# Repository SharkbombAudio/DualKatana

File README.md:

# DualKatana
Ever wanted two Katanas in a single pedal?  Well, now you can...

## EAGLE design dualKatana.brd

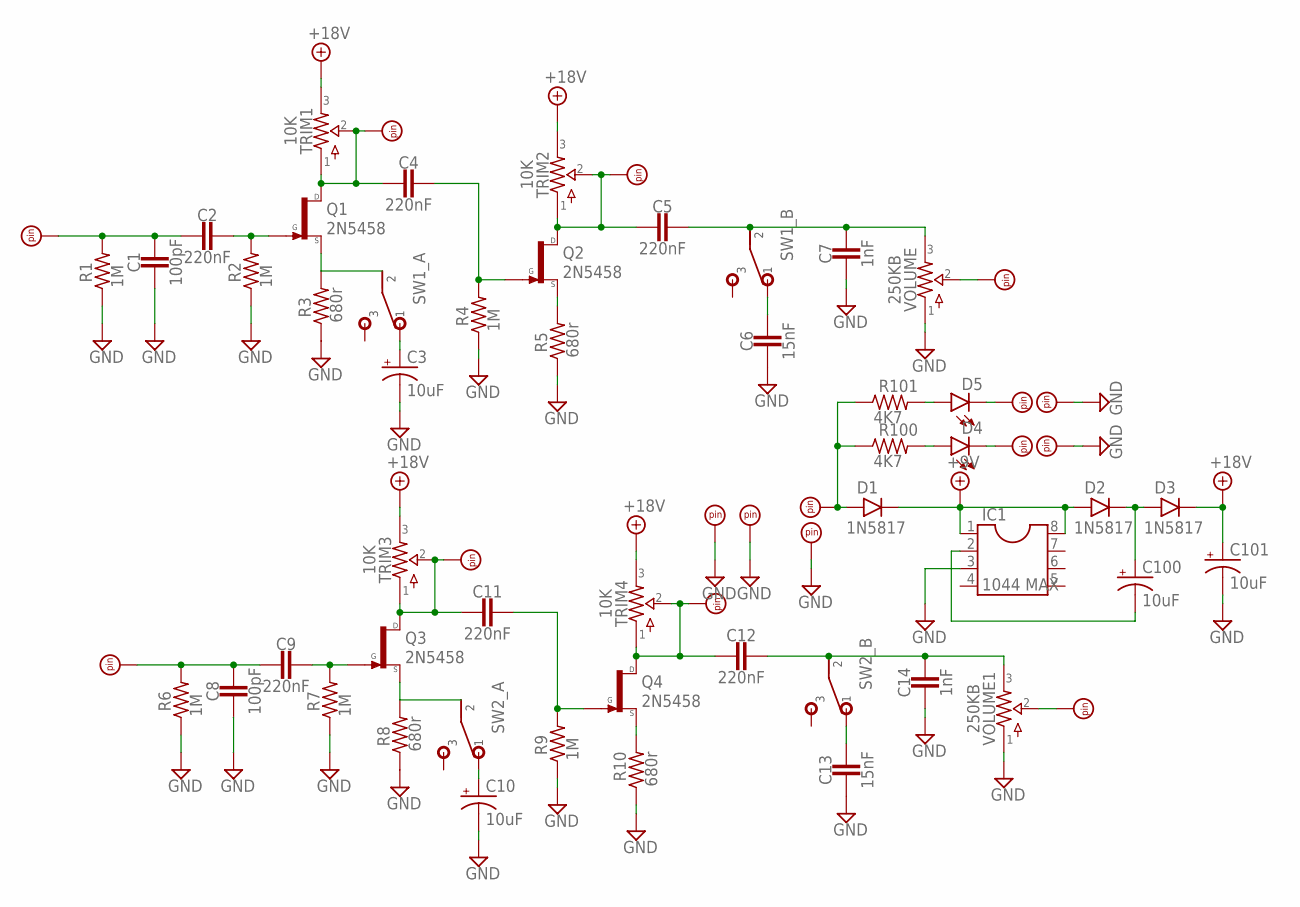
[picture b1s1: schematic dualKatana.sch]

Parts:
C1, C8: 100pF; 0.2".MED
C2, C4, C5, C9, C11, C12: 220nF; 0.2".MED
C3, C10, C100, C101: 10uF; 050_020_1
C6, C13: 15nF; 0.2".MED
C7, C14: 1nF; 0.2".MED
D1, D2, D3: 1N5817; DO41-3
D4, D5: LED3MM
IC1: 1044 MAX; DIL08
Q1, Q2, Q3, Q4: 2N5458; TO92
R1, R2, R4, R6, R7, R9: 1M; R0207/3
R3, R5, R8, R10: 680r; R0207/3
R100, R101: 4K7; R0207/3
SW1, SW2: DPDTDPDT_3; DPDT2_PCB
TRIM1, TRIM2, TRIM3, TRIM4: 10K; TRIM3
U$1, U$2, U$3, U$4, U$5, U$6, U$7, U$8, U$9, U$10, U$11, U$12, U$13, U$14, U$18, U$19: PADS.RND_NL; PAD2
VOLUME, VOLUME1: 250KB; 16MM_B.MOUNT

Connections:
+9V: D1.C, D2.A, IC1.1, IC1.8
+18V: C101.+, D3.C, TRIM1.3, TRIM1.6 (3), TRIM2.3, TRIM2.6 (3), TRIM3.3, TRIM3.6 (3), TRIM4.3, TRIM4.6 (3)
GND: C1.2, C3.-, C6.2, C7.2, C8.2, C10.-, C13.2, C14.2, C101.-, IC1.3, R1.1, R2.1, R3.1, R4.1, R5.1, R6.1, R7.1, R8.1, R9.1, R10.1, U$2.P$1, U$5.P$1, U$6.P$1, U$18.P$1, U$19.P$1, VOLUME.1, VOLUME1.1
unnamed: D1.A, R100.1, R101.1, U$1.P$1
unnamed: C1.1, C2.2, R1.2, U$7.P$1
unnamed: C100.-, IC1.2
unnamed: C100.+, D2.C, D3.A
unnamed: D4.A, R100.2
unnamed: D5.A, R101.2
unnamed: D4.K (C), U$3.P$1
unnamed: D5.K (C), U$4.P$1
unnamed: C2.1, Q1.3 (G), R2.2
unnamed: Q1.2 (S), R3.2, SW1.A2 (2)
unnamed: C3.+, SW1.A1 (1)
unnamed: C4.2, Q1.1 (D), TRIM1.1, TRIM1.2, TRIM1.4 (1), TRIM1.5 (2), U$8.P$1
unnamed: C4.1, Q2.3 (G), R4.2
unnamed: Q2.2 (S), R5.2
unnamed: C5.2, Q2.1 (D), TRIM2.1, TRIM2.2, TRIM2.4 (1), TRIM2.5 (2), U$9.P$1
unnamed: C5.1, C7.1, SW1.B2 (2), VOLUME.3
unnamed: C6.1, SW1.B1 (1)
unnamed: C8.1, C9.2, R6.2, U$11.P$1
unnamed: U$10.P$1, VOLUME.2
unnamed: C9.1, Q3.3 (G), R7.2
unnamed: Q3.2 (S), R8.2, SW2.A2 (2)
unnamed: C10.+, SW2.A1 (1)
unnamed: C11.2, Q3.1 (D), TRIM3.1, TRIM3.2, TRIM3.4 (1), TRIM3.5 (2), U$12.P$1
unnamed: C11.1, Q4.3 (G), R9.2
unnamed: Q4.2 (S), R10.2
unnamed: C12.2, Q4.1 (D), TRIM4.1, TRIM4.2, TRIM4.4 (1), TRIM4.5 (2), U$13.P$1
unnamed: C12.1, C14.1, SW2.B2 (2), VOLUME1.3
unnamed: C13.1, SW2.B1 (1)
unnamed: U$14.P$1, VOLUME1.2

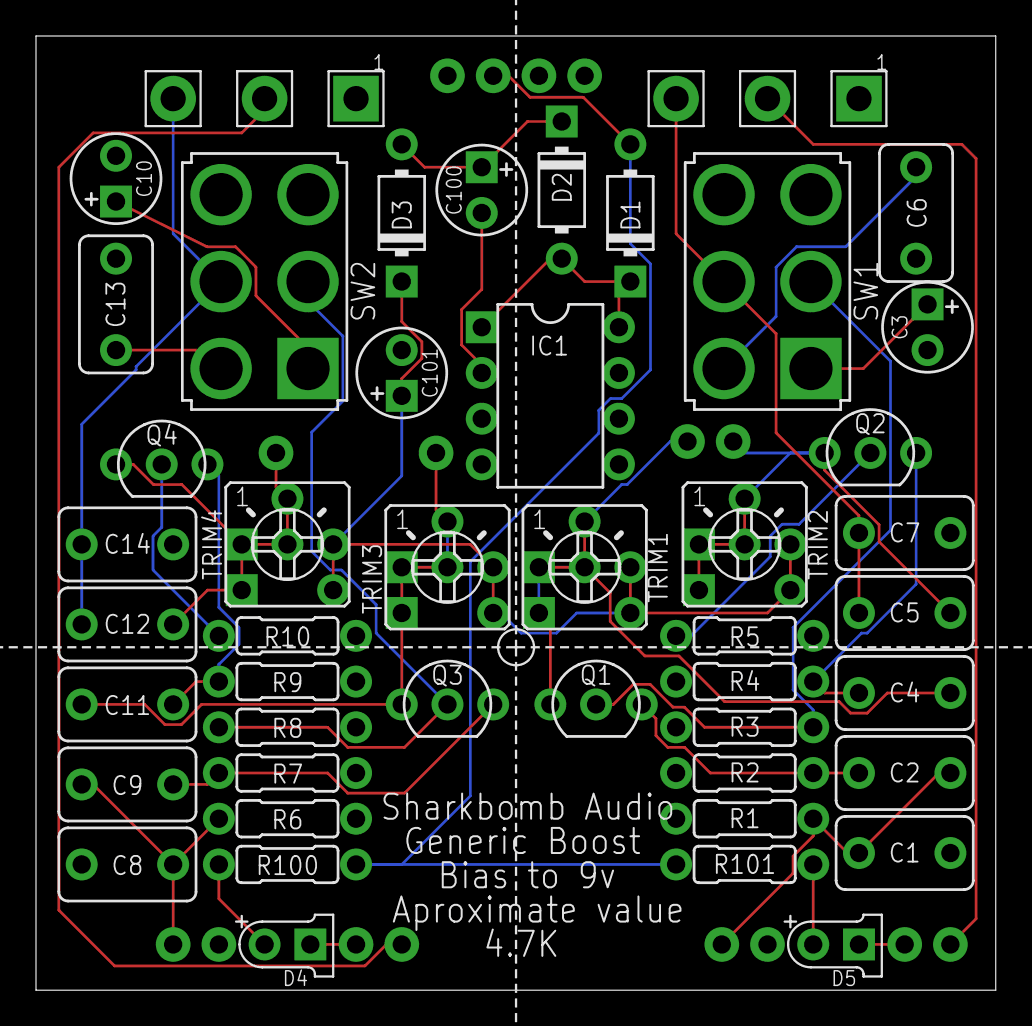
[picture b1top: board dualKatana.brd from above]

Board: 2 copper layers, 53.3 x 53.0 mm, 67 parts (0 on the bottom side), 32 nets.

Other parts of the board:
U$15: 125B
U$16, U$17: 3PDT
U$20, U$21: LED

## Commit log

2023-02-15 Eagle schematic and board for the Dual Katana
